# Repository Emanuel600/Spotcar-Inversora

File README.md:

# Spotcar Inversora
Projeto TCC, constituindo uma repuxadeira elétrica. Planilha de cálculo no arquivo Planilha_de_Cálculo.pynb; separado nas seguintes partes:
 - "Kicad - Projects" - placas que serão construídas, inclui versões alternativas que não serão utilizadas
 - "Spotcar Codebase" - código do microcontrolador escolhido

## Visão Geral
 - Visa principalmente reduzir volume, peso e custo do produto atualmente no mercado (50x40x40cm e 19,5 kg)
 - Deve ser capaz de realizar solda por resistência através da ponteira de solda (mínimo 10A, máximo ~200A)
 - Utilizada para desamassar peças metálicas de carros - não recomendada para lataria de alumínio

## Especificações Técnicas do Sistema
 - Tensão de entrada 220 V @ 60 Hz
 - Potência nominal de saída 2 kVA
 - Corrente máxima de saída 200 A
 - Frequência da corrente de saída 40 kHz
 - Tensão RMS de saída em vazio 10 V (onda quadrada)
 - Tecnologia inversora (Dada a potência, provável o uso de IGBTs)
 - Proteção de sobrecorrente, sobretemperatura e possívelmente subtensão na entrada

## Topologia
Devido à potência relativamente baixa e para reduzir a complexidade do comando - foi escolhida a topologia meia ponte.

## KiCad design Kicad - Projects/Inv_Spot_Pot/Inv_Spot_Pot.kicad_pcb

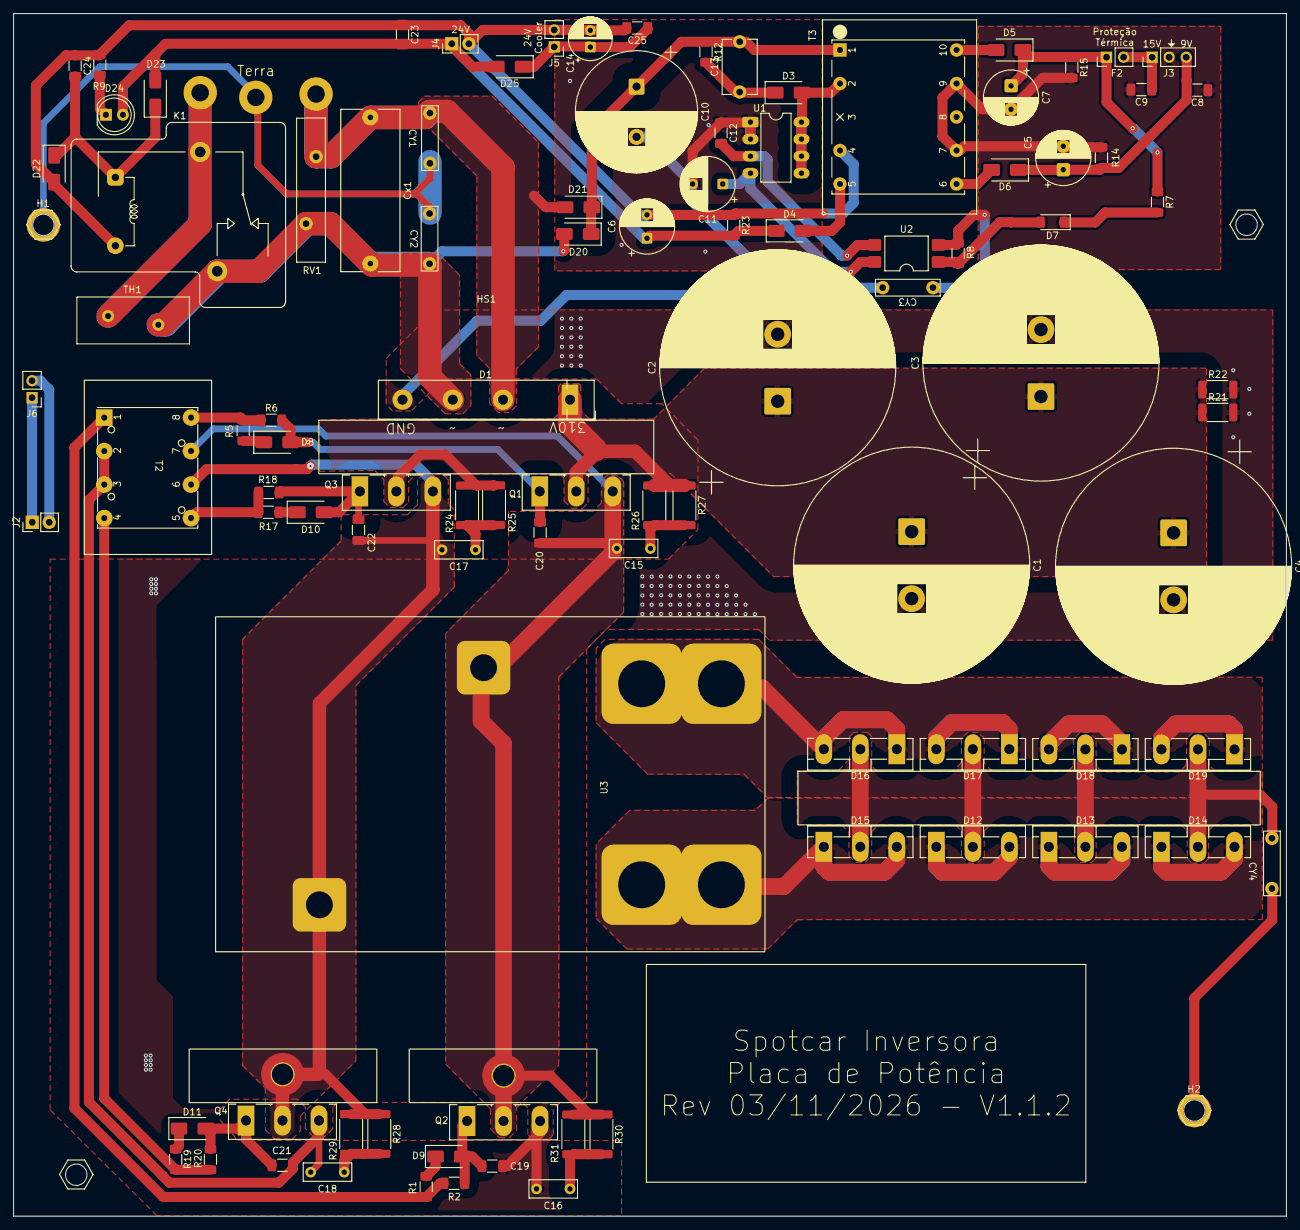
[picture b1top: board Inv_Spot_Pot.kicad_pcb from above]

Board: 2 copper layers, 190.0 x 179.5 mm, 108 parts (0 on the bottom side), 48 nets.

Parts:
C1, C2, C3, C4: 680u; CP_Radial_D35.0mm_P10.00mm_SnapIn
C5, C6, C7: 220u; CP_Radial_D8.0mm_P3.50mm
C8, C9, C23, C24, C25: 100n; C_1206_3216Metric_Pad1.33x1.80mm_HandSolder
C10: 100u; CP_Radial_D18.0mm_P7.50mm
C11: 47u; CP_Radial_D8.0mm_P3.50mm
C12: 1n; C_1206_3216Metric_Pad1.33x1.80mm_HandSolder
C13: 4.7n; C_Disc_D8.0mm_W5.0mm_P7.50mm
C14: 47u; CP_Radial_D6.3mm_P2.50mm
C15, C16, C17, C18: 4.7n; C_Disc_D7.0mm_W2.5mm_P5.00mm
C19, C20, C21, C22: 10n; C_1206_3216Metric_Pad1.33x1.80mm_HandSolder
CY1, CY2, CY3, CY4: C; C_Disc_D7.0mm_W2.5mm_P7.50mm
Cx1: C; C_Rect_L24.0mm_W8.6mm_P22.50mm_MKT
D1: HD50SB100; Diode_Bridge_32.0x5.6x17.0mm_P10.0mm_P7.5mm
D3, D4, D5, D6: US1M; D_SMA
D7: BZV55B12; D_MiniMELF
D8, D9, D10, D11: SS16; D_SMA
D12, D13, D14, D15, D16, D17, D18, D19: MUR80G20; TO-3P-3_Vertical
D20, D21, D22, D23, D25: M7; D_SMA
D24: LED; LED_D5.0mm_Clear
F2: Polyfuse; PinHeader_1x02_P2.54mm_Vertical
H1, H2: MountingHole_Pad; Hexagonal-M3-Padded
H3, H4: MountingHole; Hexagonal-M3
H9, H10: MountingHole_Pad; MountingHole_3.2mm_M3_Pad_TopOnly
HS1: Heatsink; Floating_50x8x62mm
HS2, HS3: Heatsink; Floating_28x15x70mm
HS4: Heatsink; Floating_69x33x62mm
J2, J6: PWM; PinHeader_1x02_P2.54mm_Vertical
J3: Display_Power; PinHeader_1x03_P2.54mm_Vertical
J4, J5: 24V; PinHeader_1x02_P2.54mm_Vertical
K1: Y14x-1C-xxDS; Relay_SPDT_RAYEX-L90
Q1, Q2, Q3, Q4: 60N60; TO-247-3_Vertical
R1, R5, R17, R19: 5.1; R_1206_3216Metric_Pad1.30x1.75mm_HandSolder
R2, R6, R18, R20: 20; R_1206_3216Metric_Pad1.30x1.75mm_HandSolder
R7: 1k8; R_1206_3216Metric_Pad1.30x1.75mm_HandSolder
R8, R9, R12: 2k2; R_1206_3216Metric_Pad1.30x1.75mm_HandSolder
R14, R15, R23: 10k; R_1206_3216Metric_Pad1.30x1.75mm_HandSolder
R21, R22: 200k; R_2010_5025Metric
R24, R25, R26, R27, R28, R29, R30, R31: 47; R_2512_6332Metric
RV1: Varistor; RV_Disc_D21.5mm_W4.3mm_P10mm
T2: Pulse_Transformer-EEL-25_26x20-4_Windings
T3: Transformer_Breve_TEZ-28x33
TH1: Thermistor_PTC; RV_Disc_D16.5mm_W6.7mm_P7.5mm
Terra: 2.5mm_Wire
U1: DIP-8_W7.62mm_LongPads
U2: LTV-817S; SMDIP-4_W9.53mm
U3: Sample-50x69.5-Double_Secondary

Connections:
7V: C5.1, C8.2, D6.1 (K), J3.3, R14.2
15V: C9.1, F2.2, J3.1
24V: C6.1, C23.2, D4.1 (K), D23.2 (A), D24.2 (A), D25.2 (A), J4.1, R23.2
24V-Cooler: C14.1, C25.1, D25.1 (K), J5.1
310V: C1.1, C2.1, C3.1, C4.1, D1.1 (+), Q1.2 (C), Q3.2 (C), R21.1, R22.1, R24.1, R25.1, R26.1, R27.1
310_{Aux}: C10.1, C13.2, D20.1 (K), D21.1 (K), R12.1, T3.1
/PWM_H: J2.1, J6.1
/PWM_L: J2.2, J6.2
/Soft_Start-24V/AC_{1}: K1.5, TH1.1
/Soft_Start-24V/AC_{2}: CY1.1, Cx1.1, D1.2, D20.2 (A), RV1.1
/Soft_Start-24V/~AC{1}: CY2.2, Cx1.2, D1.3, D21.2 (A), K1.1, RV1.2, TH1.2
Earth: C1.2, C2.2, C3.2, C4.2, C10.2, C11.2, C12.1, C16.2, C18.2, C19.1, C21.2, CY3.2, D1.4 (-), Q2.3 (E), Q4.3 (E), R21.2, R22.2, T2.2, T2.3, U1.1 (GND), U1.2 (GND)
Earth_Protective: CY1.2, CY2.1, CY4.2, H1.1 (1_1), H2.1 (1_1), Terra.1
GND: C5.2, C7.2, C8.1, C9.2, CY3.1, J3.2, R8.2, R14.1, R15.2, T3.7, T3.9, U2.2
GND_{24}: C6.2, C14.2, C23.1, C24.1, C25.2, D22.2 (A), J4.2, J5.2, K1.3, R9.2, R23.1, T3.4
Gate: C20.1, D8.2 (A), Q1.1 (G), R6.1
Gate1: C22.1, D10.2 (A), Q3.1 (G), R18.1
unnamed: C15.1, R26.2, R27.2
unnamed: C16.1, R30.2, R31.2
unnamed: C17.1, R24.2, R25.2
unnamed: C18.1, R28.2, R29.2
unnamed: D3.2 (A), T3.2, U1.5 (drain), U1.6 (drain), U1.7 (drain), U1.8 (drain)
unnamed: C13.1, D3.1 (K), R12.2
unnamed: D4.2 (A), T3.5
unnamed: D5.2 (A), T3.10
unnamed: C7.1, D5.1 (K), F2.1, R7.1, R15.1
unnamed: D6.2 (A), T3.6
unnamed: D7.2 (A), R8.1, U2.1
unnamed: D7.1 (K), R7.2
unnamed: D8.1 (K), R5.1
unnamed: D9.1 (K), R1.1
unnamed: D10.1 (K), R17.1
unnamed: D11.1 (K), R19.1
unnamed: C24.2, D22.1 (K), D23.1 (K), K1.4
unnamed: D24.1 (K), R9.1
unnamed: C12.2, U1.3 (FB), U2.3
unnamed: C11.1, U1.4 (Vcc), U2.4
Out1: D12.1 (K), D12.3 (K), D13.1 (K), D13.3 (K), D14.1 (K), D14.3 (K), D15.1 (K), D15.3 (K), U3.3, U3.5
Out2: D16.1 (K), D16.3 (K), D17.1 (K), D17.3 (K), D18.1 (K), D18.3 (K), D19.1 (K), D19.3 (K), U3.4, U3.6
Out+: CY4.1, D12.2 (A), D13.2 (A), D14.2 (A), D15.2 (A), D16.2 (A), D17.2 (A), D18.2 (A), D19.2 (A)
PWM: R5.2, R6.2, T2.8
PWM1: R17.2, R18.2, T2.5
T+: C17.2, C22.2, H10.1 (1_1), Q3.3 (E), Q4.2 (C), R28.1, R29.1, T2.6, U3.1
T-: C15.2, C20.2, H9.1 (1_1), Q1.3 (E), Q2.2 (C), R30.1, R31.1, T2.7, U3.2
~Gate1: C21.1, D11.2 (A), Q4.1 (G), R20.1
~Gate: C19.2, D9.2 (A), Q2.1 (G), R2.1
~PWM1: R19.2, R20.2, T2.4
~PWM: R1.2, R2.2, T2.1

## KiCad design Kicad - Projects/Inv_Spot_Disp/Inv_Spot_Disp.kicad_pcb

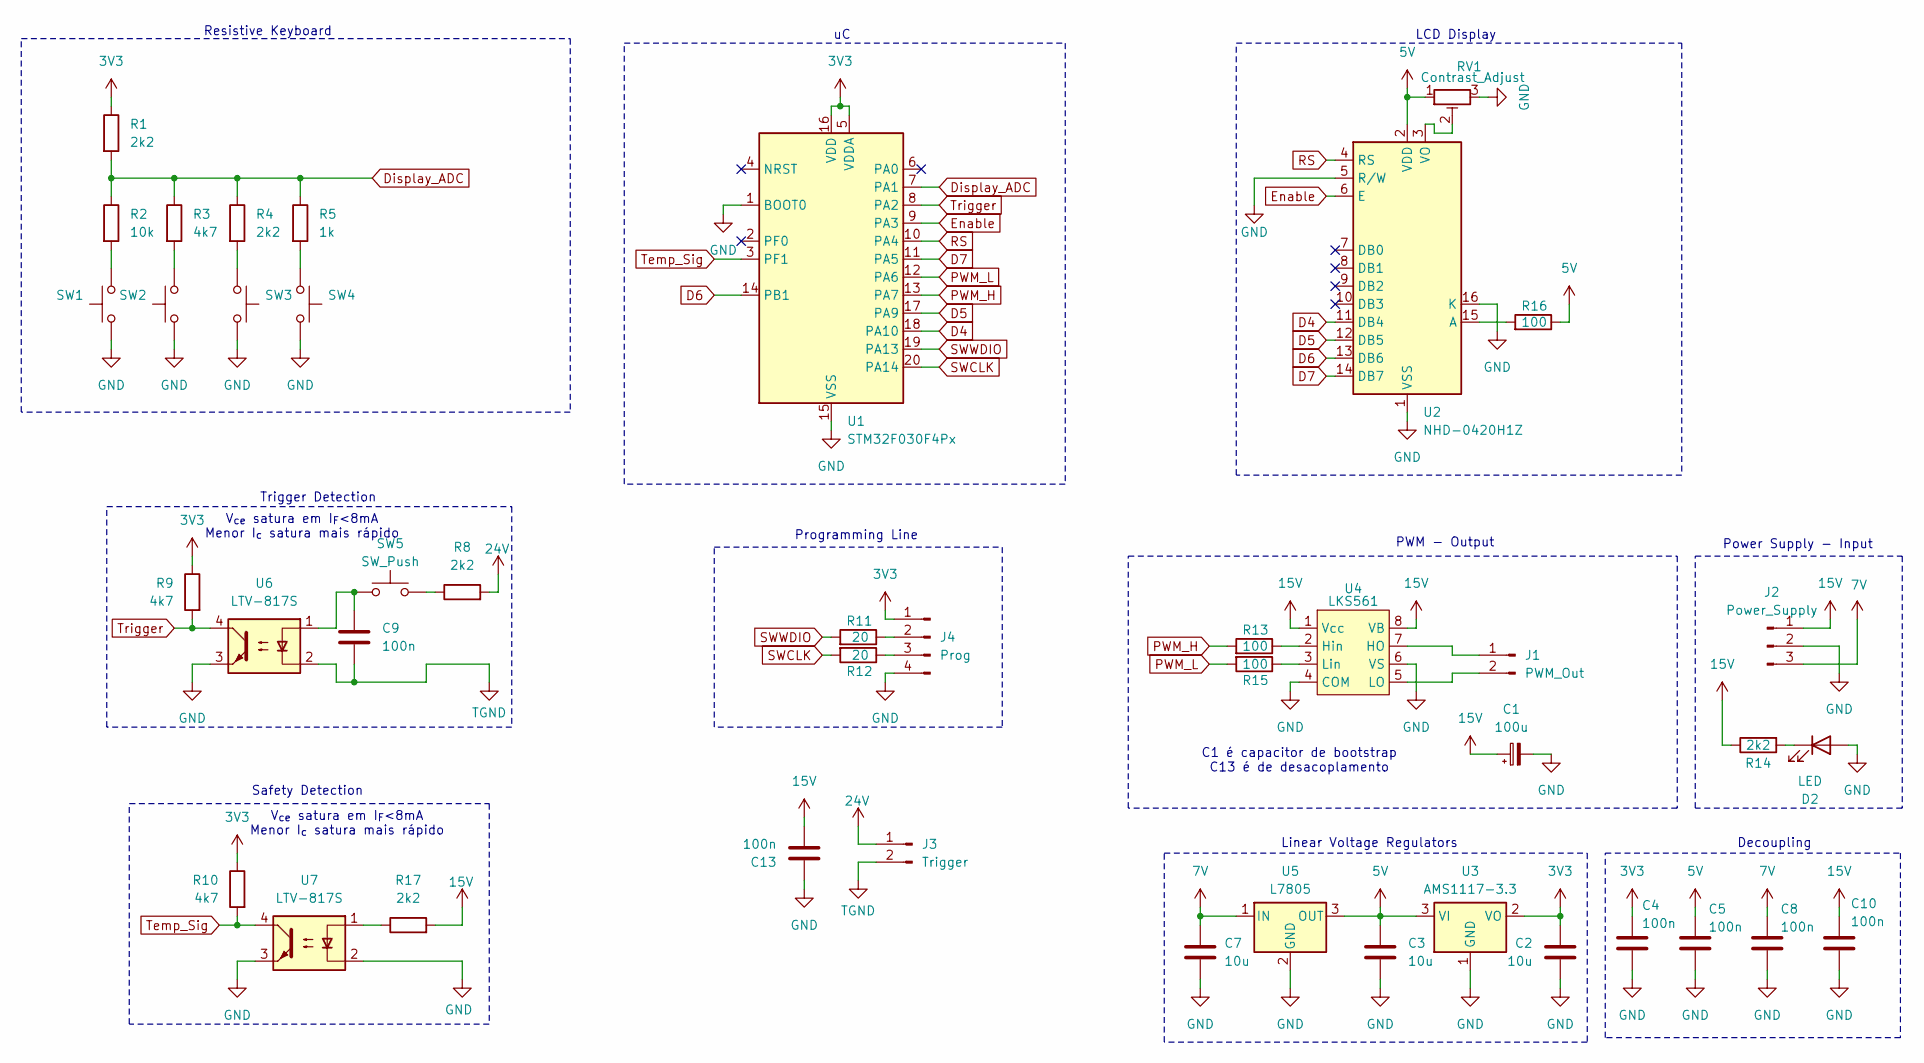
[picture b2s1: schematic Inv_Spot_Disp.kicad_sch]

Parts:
C1: 100u; CP_Radial_D10.0mm_P5.00mm
C2, C3, C7: 10u; CP_Radial_D10.0mm_P5.00mm
C4, C5, C8, C9, C10, C13: 100n; C_1206_3216Metric_Pad1.33x1.80mm_HandSolder
D2: LED; LED_D5.0mm
J1: PWM_Out; PinHeader_1x02_P2.54mm_Vertical
J2: Power_Supply; PinHeader_1x03_P2.54mm_Vertical
J3: Trigger; PinHeader_1x02_P2.54mm_Vertical
J4: Prog; PinHeader_1x04_P2.54mm_Vertical
R1, R4, R8, R14, R17: 2k2; R_1206_3216Metric_Pad1.30x1.75mm_HandSolder
R2: 10k; R_1206_3216Metric_Pad1.30x1.75mm_HandSolder
R3, R9, R10: 4k7; R_1206_3216Metric_Pad1.30x1.75mm_HandSolder
R5: 1k; R_1206_3216Metric_Pad1.30x1.75mm_HandSolder
R11, R12: 20; R_1206_3216Metric_Pad1.30x1.75mm_HandSolder
R13, R15, R16: 100; R_1206_3216Metric
RV1: Contrast_Adjust; Potentiometer_Bourns_3266Y_Vertical
SW1, SW2, SW3, SW4: Push_Button; SW_PUSH_6mm_H13mm
SW5: SW_Push; SW_PUSH_1P1T_6x3.5mm_H4.3_APEM_MJTP1243
U1: STM32F030F4Px; TSSOP-20_4.4x6.5mm_P0.65mm
U2: NHD-0420H1Z; WC1602A
U3: AMS1117-3.3; SOT-223-3_TabPin2
U4: LKS561; SSOP-8_3.9x5.05mm_P1.27mm
U5: L7805; TO-252-2
U6, U7: LTV-817S; SMDIP-4_W9.53mm

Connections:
3V3: C2.1, C4.1, J4.1, R1.1, R9.1, R10.1, U1.5 (VDDA), U1.16 (VDD), U3.2 (VO)
5V: C3.1, C5.1, R16.1, RV1.1, U2.2 (VDD), U3.3 (VI), U5.3 (OUT)
7V: C7.1, C8.1, J2.3, U5.1 (IN)
15V: C1.1, C10.1, C13.2, J2.1, R14.1, R17.2, U4.1 (Vcc), U4.8 (VB)
24V: J3.1, R8.2
D4: U1.18 (PA10), U2.11 (DB4)
D5: U1.17 (PA9), U2.12 (DB5)
D6: U1.14 (PB1), U2.13 (DB6)
D7: U1.11 (PA5), U2.14 (DB7)
Display_ADC: R1.2, R2.1, R3.1, R4.1, R5.1, U1.7 (PA1)
Enable: U1.9 (PA3), U2.6 (E)
GND: C1.2, C2.2, C3.2, C4.2, C5.2, C7.2, C8.2, C10.2, C13.1, D2.2 (A), J2.2, J4.4, RV1.3, SW1.1, SW2.1, SW3.1, SW4.1, U1.1 (BOOT0), U1.15 (VSS), U2.1 (VSS), U2.5 (R/W), U2.16 (K), U3.1 (GND), U4.4 (COM), U4.6 (VS), U5.2 (GND), U6.3, U7.2, U7.3
unnamed: C9.1, SW5.1, U6.1
unnamed: D2.1 (K), R14.2
unnamed: J1.1, U4.7 (HO)
unnamed: J1.2, U4.5 (LO)
unnamed: J4.2, R11.1
unnamed: J4.3, R12.1
unnamed: R2.2, SW1.2
unnamed: R3.2, SW2.2
unnamed: R4.2, SW3.2
unnamed: R5.2, SW4.2
unnamed: R8.1, SW5.2
unnamed: R17.1, U7.1
unnamed: R16.2, U2.15 (A)
unnamed: RV1.2, U2.3 (VO)
unnamed: R13.1, U4.2 (Hin)
unnamed: R15.1, U4.3 (Lin)
PWM_H: R13.2, U1.13 (PA7)
PWM_L: R15.2, U1.12 (PA6)
RS: U1.10 (PA4), U2.4 (RS)
SWCLK: R12.2, U1.20 (PA14)
SWWDIO: R11.2, U1.19 (PA13)
TGND: C9.2, J3.2, U6.2
Temp_Sig: R10.2, U1.3 (PF1), U7.4
Trigger: R9.2, U1.8 (PA2), U6.4

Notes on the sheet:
Programming Line
PWM - Output
Safety Detection
Linear Voltage Regulators
C1 é capacitor de bootstrap C13 é de desacoplamento
V_{ce} satura em I_{F}<8mA Menor I_{c} satura mais rápido
Decoupling
Power Supply - Input
Trigger Detection
LCD Display
Resistive Keyboard

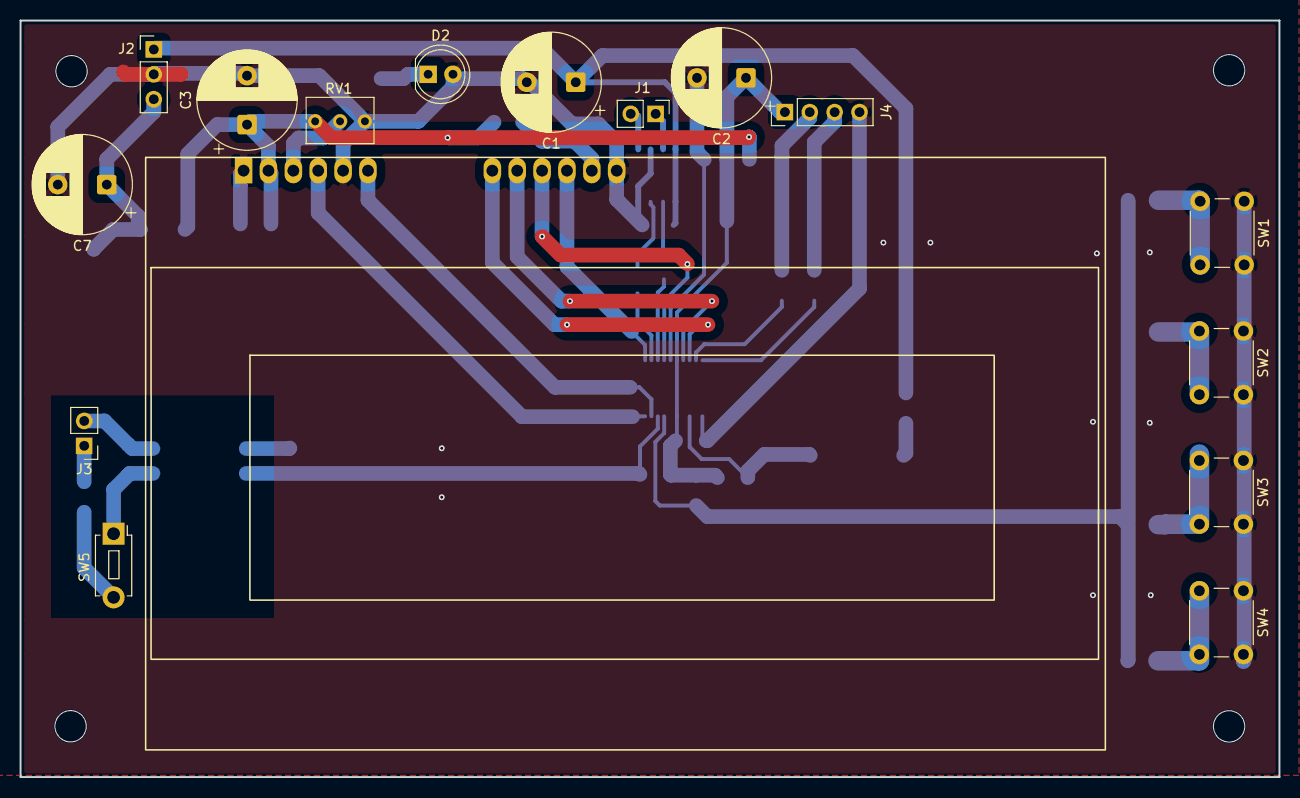
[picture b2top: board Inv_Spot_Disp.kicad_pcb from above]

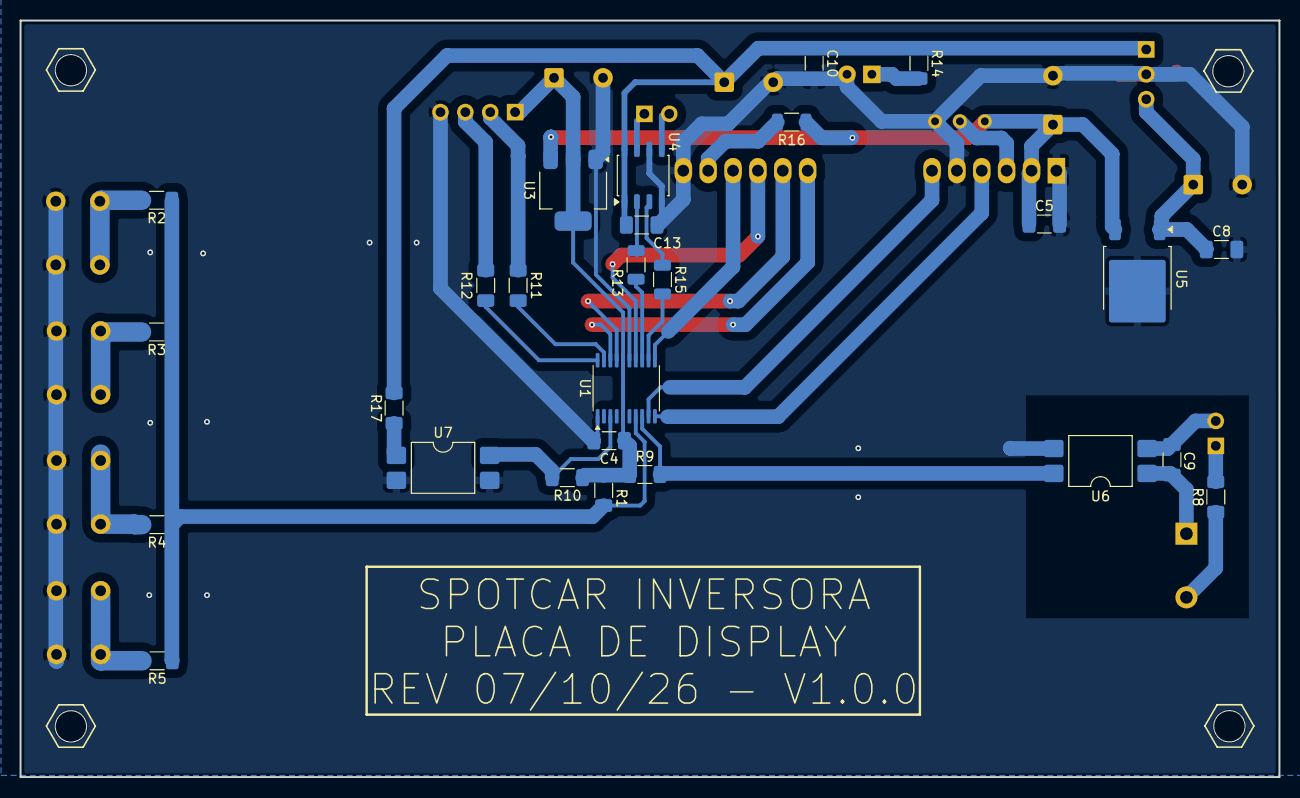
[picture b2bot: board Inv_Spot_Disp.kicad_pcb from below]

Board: 2 copper layers, 128.6 x 77.2 mm, 43 parts (27 on the bottom side), 36 nets.

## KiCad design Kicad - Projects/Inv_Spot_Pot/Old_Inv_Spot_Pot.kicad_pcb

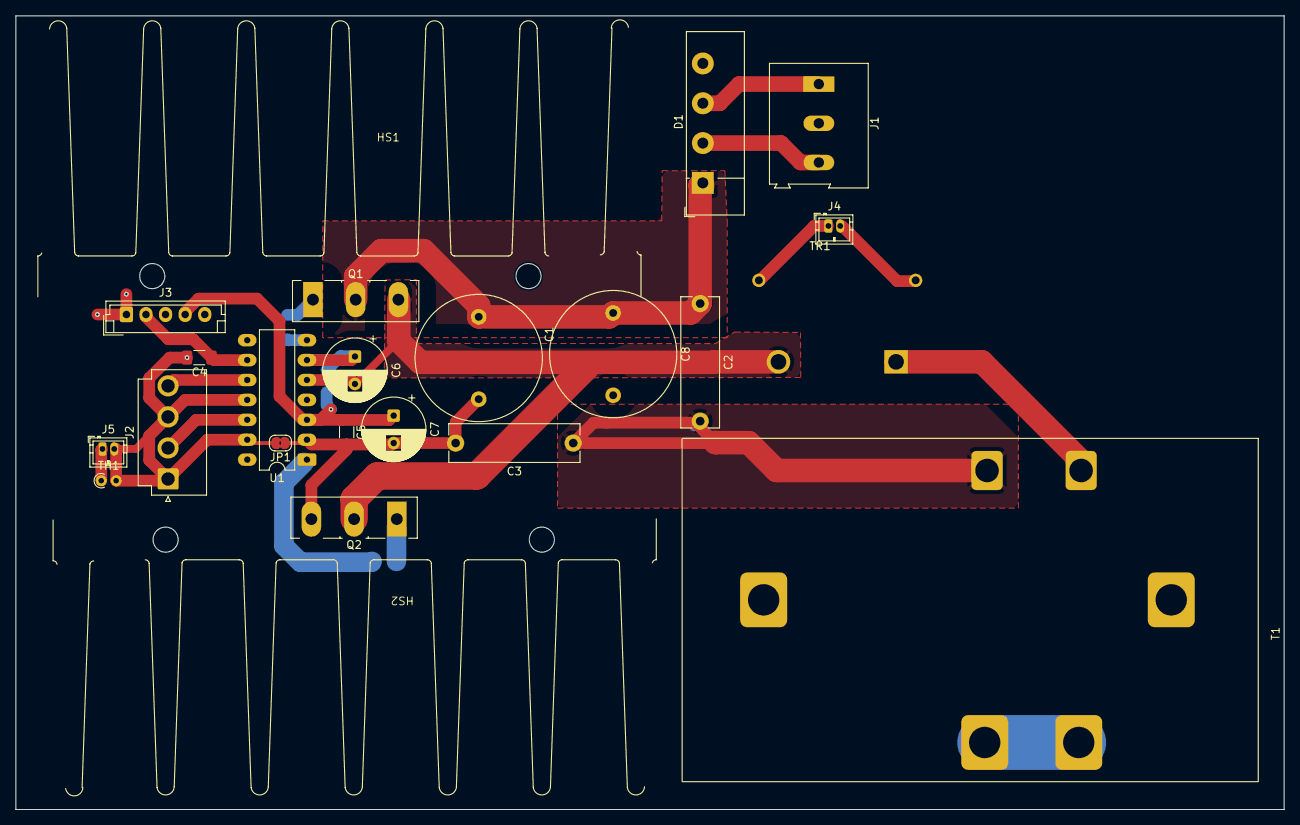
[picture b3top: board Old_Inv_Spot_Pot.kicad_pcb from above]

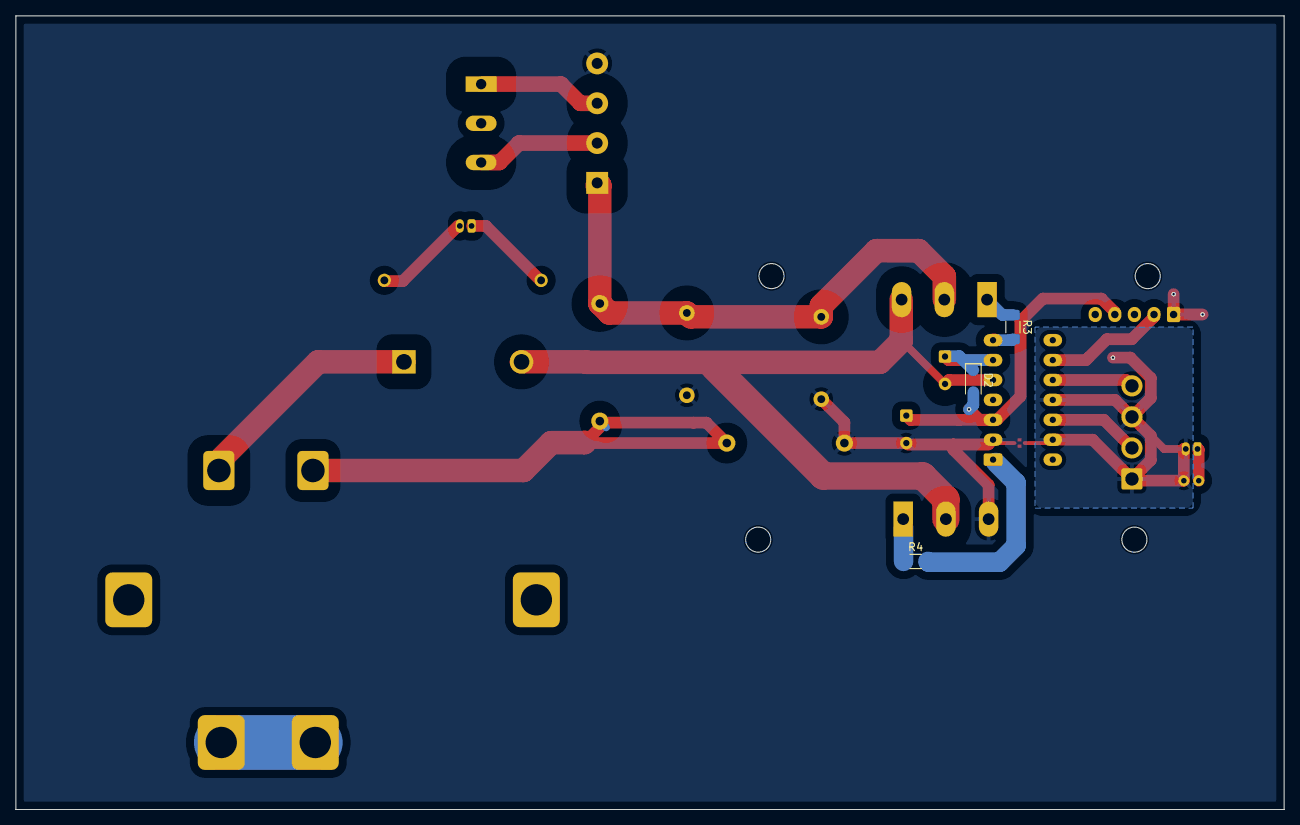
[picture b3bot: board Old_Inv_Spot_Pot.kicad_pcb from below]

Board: 2 copper layers, 161.8 x 101.2 mm, 26 parts (3 on the bottom side), 21 nets.

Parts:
C1, C8: 220u; C_Radial_D16.0mm_H25.0mm_P7.50mm
C2, C3: 1u; C_Rect_L16.5mm_W4.7mm_P15.00mm_MKT
C4, C5: 100n; C_1206_3216Metric_Pad1.33x1.80mm_HandSolder
C6, C7: 10u; CP_Radial_D8.0mm_P3.50mm
D1: KBU4M; Diode_Bridge_Vishay_KBU
D2: D_Schottky; D_SOD-123F
HS1, HS2: Heatsink; Heatsink_81x32
J1: Screw_Terminal_01x03; TerminalBlock_Altech_AK300-3_P5.00mm
J2: PWM; JST_VH_B4P-VH-B_1x04_P3.96mm_Vertical
J3: Power_Supply; JST_EH_B5B-EH-A_1x05_P2.50mm_Vertical
J4: Current_Sense; JST_ZH_B2B-ZR_1x02_P1.50mm_Vertical
J5: Temperature_Sense; JST_ZH_B2B-ZR_1x02_P1.50mm_Vertical
JP1: Link; SolderJumper-2_P1.3mm_Bridged2Bar_RoundedPad1.0x1.5mm
Q1, Q2: 40T120; TO-247-3_Vertical
R3, R4: 10; R_1206_3216Metric_Pad1.30x1.75mm_HandSolder
T1: Transformer_1P_2S; Transformer_Toroid_THT_7032
TH1: Thermistor_NTC; R_Axial_DIN0204_L3.6mm_D1.6mm_P1.90mm_Vertical
TR1: TR60_FC; Current_Transformer-1_200-21x20
U1: IR2110; DIP-14_W7.62mm_LongPads

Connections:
5V: C4.1, J3.2, U1.9 (VDD)
15V: C5.1, C7.1, D2.2 (A), J3.4, U1.3 (VCC)
310V: C1.1, C2.1, C8.1, D1.1 (+), Q1.2 (C)
/PWM_H: J2.4, U1.10 (HIN)
/PWM_L: J2.2, U1.12 (LIN)
Earth: C1.2, C3.2, C5.2, C7.2, C8.2, D1.4 (-), J3.1, JP1.1 (A), Q2.3 (E), U1.2 (COM)
GND: C4.2, J2.1, J2.3, J5.2, JP1.2 (B), TH1.2, U1.11 (SD), U1.13 (VSS)
unnamed: C6.1, D2.1 (K), U1.6 (VB)
unnamed: D1.3, J1.1
unnamed: D1.2, J1.3
unnamed: J4.1, TR1.4
unnamed: J4.2, TR1.3
unnamed: J5.1, TH1.1
unnamed: Q1.1 (G), R3.1
unnamed: Q2.1 (G), R4.1
unnamed: T1.1 (AA), TR1.1
unnamed: T1.4 (SB), T1.5 (SC)
unnamed: R3.2, U1.7 (HO)
unnamed: R4.2, U1.1 (LO)
T+: C2.2, C3.1, T1.2 (AB)
T-: C6.2, Q1.3 (E), Q2.2 (C), TR1.2, U1.5 (VS)

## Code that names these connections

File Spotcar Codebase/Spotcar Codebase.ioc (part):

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Mcu.Name=STM32F030F4Px
Mcu.Package=TSSOP20
Mcu.UserName=STM32F030F4Px
PA1.GPIOParameters=GPIO_Label
PA1.GPIO_Label=Display_ADC
PA1.Mode=IN1
PA1.Signal=ADC_IN1
PA10.GPIOParameters=GPIO_Label
PA10.GPIO_Label=D4
PA10.Signal=GPIO_Output
PA13.Mode=Serial_Wire
PA13.Signal=SYS_SWDIO
PA14.Mode=Serial_Wire
PA14.Signal=SYS_SWCLK
PA2.GPIOParameters=GPIO_Label
PA2.GPIO_Label=Trigger
PA2.Signal=GPIO_Input
PA3.GPIOParameters=GPIO_Label
PA3.GPIO_Label=Enable
PA3.Signal=GPIO_Output
PA4.GPIOParameters=GPIO_Label
PA4.GPIO_Label=RS
PA4.Signal=GPIO_Output
PA5.GPIOParameters=GPIO_Label
PA5.GPIO_Label=D7
PA5.Signal=GPIO_Output
PA6.Signal=S_TIM3_CH1
PA7.Mode=PWM Generation1 CH1N
PA7.Signal=TIM1_CH1N
PA9.GPIOParameters=GPIO_Label
PA9.GPIO_Label=D5
PA9.Signal=GPIO_Output
PB1.GPIOParameters=GPIO_Label
PB1.GPIO_Label=D6
PB1.Signal=GPIO_Output
PF1-OSC_OUT.GPIOParameters=GPIO_Label
PF1-OSC_OUT.GPIO_Label=Thermal
PF1-OSC_OUT.Signal=GPIO_Input
RCC.SYSCLKFreq_VALUE=48000000
RCC.SYSCLKSource=RCC_SYSCLKSOURCE_PLLCLK
board=custom

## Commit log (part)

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2026-03-23 First Commit
    Long overdue, includes the codebase (incomplete) and the current PBCs made with KiCAD (still WIP)
    Todo:
    Implement ADC menu again
    Check board manufacturing capabilities and wether the design is ready to go not
2026-03-23 Kicad files
    Should've been included in last commit but got hidden by a discarded git repo
2026-03-24 Updated codebase
    Added in a menu and implemented trigger functionality
2026-03-25 Criado através do Colab - planilha de cálculo do circuito que será utilizado
2026-03-25 Update README.md
    Detailed project specification - will add more in the future, probably
2026-03-27 Add reference image from simulation
    Imagem da simulação do circuito - corrente média da fonte
2026-03-31 Updated PCB
    Fixed some footprints, increased insulation and improved board segmentation - segmentation still needs some work
2026-04-10 Final revision for board with driver IC
    Última revisão da placa com driver IR2110 - para melhor flexibilidade e aproveitamento de espaço da placa, foi decidido explorar o projeto com um transformador de gate drive EE-25
    Poderia ser utilizado um transformador EE-19 e poupar espaço, mas por disponibilidade imediata foi utilizado o EEL-25
2026-04-10 Half bridge prototype
    IR2110 completamente substituído por transformador de gate, falta corrigir footprint do transformador de saída e fazer placa alternativa de ponte completa
2026-04-13 Resistor CE
    Adicionado resistor coletor-emissor na placa, corrigido erro na direção do diodo do circuito de drive dos IGBTs
    Melhora nos planos de referência - Alguns pontos ainda apresentam caminho de retorno longos, mas talvez isso possa ser corrigido na própria placa
2026-04-14 Melhora de Isolamento
    Removido parte do plano preenchido no circuito de gate drive da chave superior para manter distância do isolamento elétrico
2026-04-15 General Polishing
    Removidos furos dos dissipadores que não serão utilizados, aberto espaço previsto para relé e circuito de tensão auxiliar
    Falta ainda corrigir o footprint do transformador (bobinar) e a placa base de display que será utilizada
2026-04-20 Adicionando Fonte Auxiliar
    Fonte auxiliar com topologia flyback dimencionada, falta criar o footprint do transformador, abrir o espaço na placa e finalizar o roteamento dos componentes
2026-04-21 Adicionado Flyback (WIP)
    Adicionado circuito auxiliar flyback - footprint ocupa bastante espaço e aumenta significativamente a altura da placa.
    Revendo layout para tentar melhorar o particionamento da placa
2026-04-22 Ajuste da Auxiliar
    Fonte auxiliar ajustada, ainda não satisfeito com o resultado
2026-04-22 Primeira Versão - Ponte Completa
    Desnho inicial da placa de ponte completa
    Contém principalmente o seccionamento da placa, sem conexões próprias ainda
2026-04-22 Capacitores Ajustados
    Ajustado o footprint dos capacitores divisores de tensão (poly) para ser coerente com os 4u7 escolhidos
    Também foi adicionada uma distância entre o transformador para abrir espaço a uma ponteira de corrente
2026-04-22 Espelhados Resistores CS da Auxiliar
    Resistores CS da fonte auxiliar (R11 e R12) espelhados para reduzir um pouco o loop de corrente da linha 310V
2026-04-22 Ajustes Imediatos
    Ajustes imediatos na reunião 22/04
2026-04-23 Ajuste de Posição de Componentes
    Resistor GE da parte de baixo da inversora aproximado do emissor
    Footprint dos transformadores alterados para maior representatividade dos componentes reais
2026-04-23 Only Opened the Project
    Only opened the project
2026-04-23 Ajustes Gerais
    Alterado footprint do varistor
    Afastado capacitor Cx de uma trilha PWM
    Melhora no local de saída do sinal de corrente
2026-04-24 Redefinição do Circuito Flyback
    Circuito flyback reprojetado para o DK125
    Esquema básico do layout feito - falta apenas finalizar as conexões, verificando se é possível realizar o circuito em face simples
2026-04-26 Esquemático Básico - Fonte Auxiliar
    Feito esquemático base da fonte auxiliar
    Falta:
    - Conectar ele ao 310V/Earth (Earth por jumper)
    - Verificar se há como reduzir as trilhas no circuito de feedback
2026-04-27 Fonte Auxiliar Adicionada
    Adicionado circuito da fonte auxiliar, incluindo isolações necessárias
    Falta apenas verificar se o diodo utilizado suporta a tensão reversa de 310V e converter o modelo à ponte completa
2026-04-27 V1 meia ponte completo
    Faltando apenas alguns capacitores de segurança, a primeira versão do circuito meia-ponte é considerado completo
    A seguir será feito o circuito de ponte completa, onde será mais fácil de adicionar os capacitores de segurança
2026-04-27 Ajustes Preliminares
    Ajustes preliminares feitos na placa para modificá-la à um circuito ponte completa
    À fazer:
    - trocar posição dos IGBTs high e low-side
    - Trocar entrada do sensor de corrente para T+ (trocar posição no transformador também)
    - Adicionar filtros básicos (será unicializada a placa de display primeiro devido ao teste de carga)
2026-04-28 Melhoras na Ponte Completa
    Placa de ponte completa quase feita, falta rotear os PWMs e adicionar o cabo que leva T- ao transformador
    Removido arquivo .history devido a incomodar na hora de uppar os arquivos
2026-04-28 Ajustes Gerais
    Ajustando footprints e esquemáticos, falta ajuste final no esquemático e footprint do transformador de drive
2026-04-29 Ajustes Semi-Finais
    Adicionados circuitos de gate e capacitores de polipropileno, falta apenas o footprint final do transformador e os capacitores de segurança em Y na fonte auxiliar e saída da linha AC
2026-04-29 Final - Placa Ponte Completa
    Ajustadas todas as rotas da placa de potência por ponte completa, falta apenas adicionar test-points
2026-04-29 Melhora no Filtro
    Ajustada posição de CX1 no filtro
2026-04-29 Adicionados Testpoints
    Adicionados testpoints:
    - Gate de cada IGBT (+ emissor)
    - Tensão do barramento
    - Barramento da fonte auxiliar
    Trocado footprint do sensor de corrente para pinheader
2026-04-30 Apenas Aberto
    Projeto foi apenas aberto
2026-04-30 Ajustes de Esquemático - Display
    Ajustes no esquemático da placa de display:
    - Removido trigger do teclado resistivo
    - Melhora do circuito de detecção de corrente
    - Simplificação do circuito de drive - falta adicionar filtro RC antes da saída
    À fazer:
    - Implementar Opto para leitura digital do gatilho de disparo
2026-05-04 Ajustes de Esquemático - Display
    Feito:
    - Ajustes genéricos para melhor legibilidade
    - Implementado Opto para leitura do gatilho (com pull-up no lado do uC)
    - Trocados footprints das conexões para pinheader
    - Ajuste na trilha T- do IGBT superior
    À fazer:
2026-05-04 Ajustado Pinout - uC
    Feito:
    - Adicionado capacitor de bootstrap no driver
    - Ajustado pinout do uC, código gerador de PWM teve que ser alterado para manter ação de gate simétrica
    - Enrolado secundário do transformador
    - Discutido com Anderson sobre esquemáticos e layouts
    À fazer:
2026-05-04 Ajuste da Entrada
    Ajuste da entrada da fonte auxiliar
2026-05-04 Geração de Código
    Gerado o código para a nova geração de PWM
    Adicionados elementos na PCB
    Footprints corrigidos
2026-05-04 Ajustado Footprint LCD
    Pinos não utilizados removidos da LCD
2026-05-05 Primeiro Layout - Display
    Feito o layout preliminar da placa de display, conferir com o Anderson
    Corrigido problema com o layout do transformador (erro no símbolo utilizado levou a inversão dos IGBTs superiores)
2026-05-07 Ajustes Finais
    Ajustes em larguras de trilha da camada top
    Ajuste do footprint dos capacitores de polipropileno dos IGBTs
    Ajuste dos planos de referência
2026-05-07 Ponto de Teste Restaurado
    Alteração prévia acidentalmente removeu ponto de teste no gate (Q1), adicionado novamente
2026-05-08 Ajustes de Footprint
    Ajustadas footprints para valores disponíveis
    Falta:
    - Adicionar GND e 5V nos pinos de programação do display
    - Adicionar resistor de 5V para Temp_Sense, possibilitando leitura de temperatura
2026-05-11 Ajustes Gerais
    Ajustes Gerais
2026-05-12 Ajustes Finais
    Ajustes finais de footprints e layouts
    Considerando aumentar isolamento da trilha T- do IGBT Q2
2026-05-13 Nova Versão - Kicad
2026-05-14 Ajustes Finais
    Ajustes Finais do código, esquemáticos e layouts
    Ainda faltam ajustes finos
2026-05-15 Correção - Timers e Estimativa
    Corrigido o código que inicia a geração do PWM e que estima a corrente
    Ajustado para que o ciclo de trabalho esteja limitado à 50% no máximo e utilizando os timers corretos para geração de PWM
2026-05-15 Ajustes de Isolamento e Espaçamento
    Ajustes no isolamento de trilhas de alta tensão na placa de potência e no espaçamento dos capacitores dos IGBTs
    Ajustes nas posições de componentes na placa de display
    Ajustado ADC para aumentar período de amostragem
2026-05-15 Adicionada Calibração do ADC
    Adicionada calibração do ADC
2026-05-18 Ajustes de Esquemático / Layout
    Ajustado símbolo da chave bimetálica na linha de 15V para proteção térmica
    Ajustada trilhas de PWM que estavam sendo cobertas por um capacitor
2026-05-19 Adicionado LED - Temperatura
    Adicionado LED na linha de 15V que desliga quando proteção térmica é acionada
    Adicionados PDFs para impressão
2026-05-21 Arquivos BOM gerados
    Gerados arquivos BOM html para as placas
2026-05-21 Concertos Gerais
    Atualização da detecção do trigger e calibração do ADC, junto a mínimos comparativos de tamanho de Flash entre versões do código
2026-05-22 Ajuste de Folgas
    Aumantada folga entre elementos do filtro e de isolamento entre trilha de PWM na camada TOP e o dissipador de Q4
2026-05-22 Corrigido Cálculo Grosso da Corrente
    Cálculo da corrente retornava valores errados, corrigido
2026-05-25 Adicionada Lógica da Corrente
    Adicionada lógica simples para controle de corrente:
    caso corrente esteja acima do alvo, diminui o pulso; caso contrário, aumenta o pulso
2026-05-25 Melhor Aproximação da Corrente
    Aproxima a corrente proporcionalmente à diferença (~1% da largura máxima de pulso para 5A)
    Valor de threashold dos botões de ADC recalculados para novos valores de resistores utiliados - deve ser mais preciso agora
2026-05-25 Ajuste de Timer - delay_us
    Ajustado timer da função delay_us para TIM14, deixando TIM3 para PWM escravo
2026-05-26 Consertados Labels dos Pinos
    Label dos pinos do display agora refletem os que serão usados do módulo
    Também corrigida lógica de mascara utilizada na função de comando
2026-05-27 Adicionada Tela Inicial
    Adicionada tela inicial com informações de contato e telefone
    Corrigida lógica de controle do display
    Corrigido cálculo da corrente pelo ADC
2026-05-29 Ajustes de Documentação
    Ajustada documentação do módulo LCD e corrigido erro de máscara na função HD_Set_Cursor
    Ajustada também posição de capacitor de desacoplamento do sinal do sensor da corrente para ser mais próximo do ADC.
2026-06-09 Corrigido Footprint do Display
    Corrigido problema com o footprint do display
    Melhora o caminho de retorna das trilhas de programação
    Aumento na quantidade de vias para reduzir impedância do plano terra
2026-06-11 Adição de Vias - Placa de Display
    Adicionadas mais algumas vias na placa de display
2026-06-12 Ajustado Código do Display
    Ajustado código do display para melhor funcionamento
2026-06-12 Big Fixes
    Running out of time
2026-06-16 Fixed Trigger Detection
    Trigger detection was not using the right pins
2026-06-26 Melhora no Acionamento do Trigger
    Acionamento do trigger agora ocorre quando o circuito é fechado, não aberto.
    Adição de vias de GND na saída da fonte auxiliar.
